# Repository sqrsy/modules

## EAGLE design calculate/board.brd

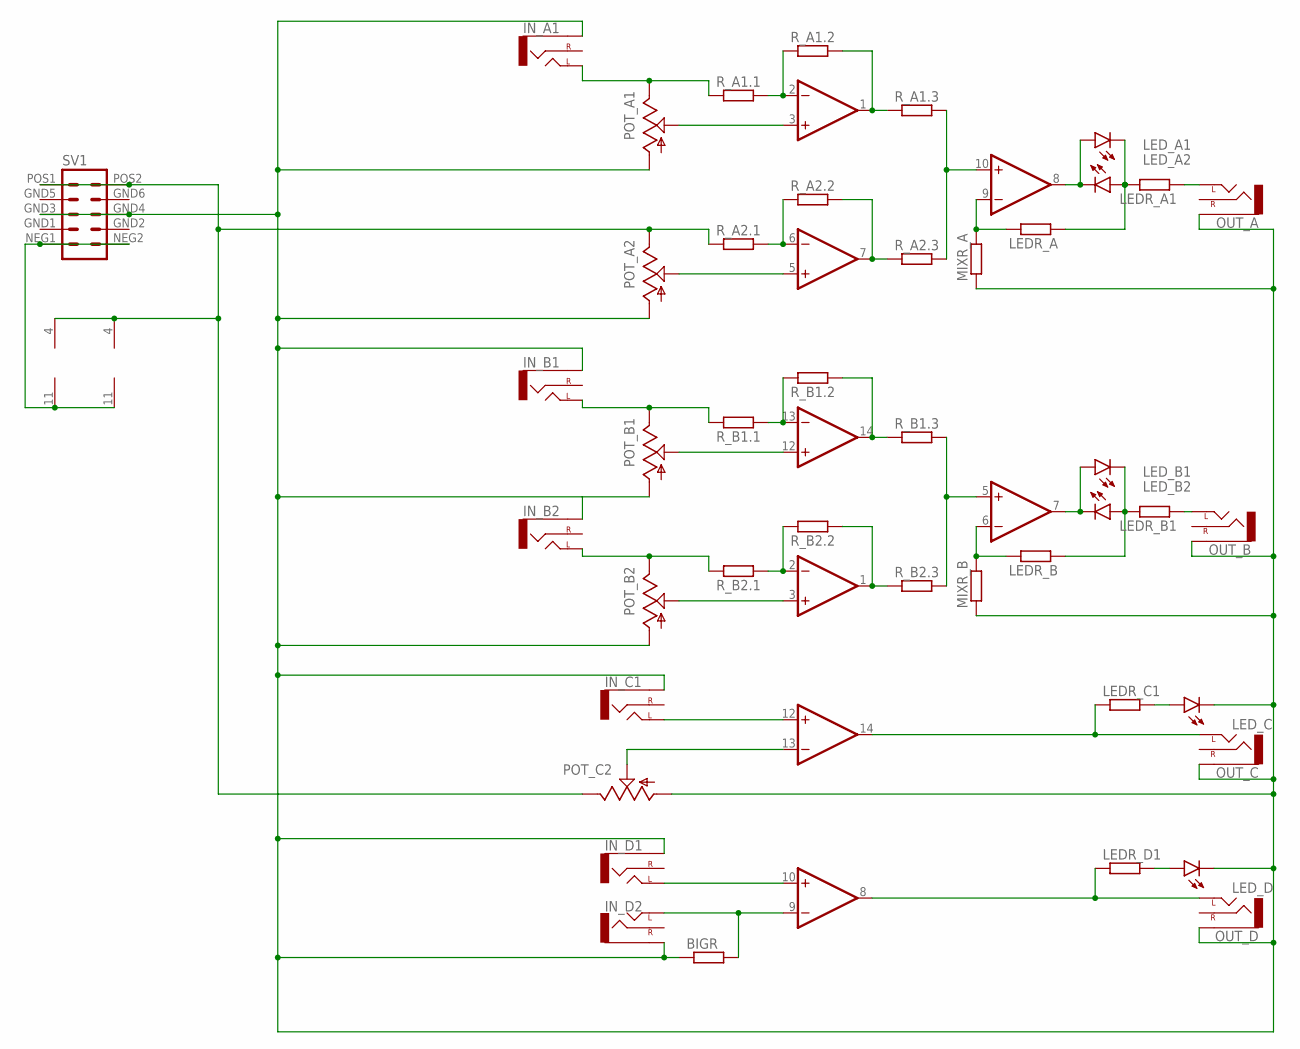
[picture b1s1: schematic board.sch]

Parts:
BIGR: RESISTOR7MM; 7MM_RESISTOR
IC1, IC2: TL074P; DIL14
IN_A1: THONKI-STEREO; WQP-PJ366ST_JACK
IN_B1, IN_B2: THONKI-STEREO; WQP-PJ366ST_JACK
IN_C1: THONKI-STEREO; WQP-PJ366ST_JACK
IN_D1, IN_D2: THONKI-STEREO; WQP-PJ366ST_JACK
LEDR_A, LEDR_A1: RESISTOR7MM; 7MM_RESISTOR
LEDR_B, LEDR_B1: RESISTOR7MM; 7MM_RESISTOR
LEDR_C1: RESISTOR7MM; 7MM_RESISTOR
LEDR_D1: RESISTOR7MM; 7MM_RESISTOR
LED_A1, LED_A2: LED3MM; LED_3MM
LED_B1, LED_B2: LED3MM; LED_3MM
LED_C: LED3MM; LED_3MM
LED_D: LED3MM; LED_3MM
MIXR_A: RESISTOR7MM; 7MM_RESISTOR
MIXR_B: RESISTOR7MM; 7MM_RESISTOR
OUT_A: THONKI-STEREO; WQP-PJ366ST_JACK
OUT_B: THONKI-STEREO; WQP-PJ366ST_JACK
OUT_C: THONKI-STEREO; WQP-PJ366ST_JACK
OUT_D: THONKI-STEREO; WQP-PJ366ST_JACK
POT_A1, POT_A2: 9MM_SNAP-IN_POT_; 9MM_SNAP-IN_POT
POT_B1, POT_B2: 9MM_SNAP-IN_POT_; 9MM_SNAP-IN_POT
POT_C2: 9MM_SNAP-IN_POT_; 9MM_SNAP-IN_POT
R_A1.1, R_A1.2, R_A1.3, R_A2.1, R_A2.2, R_A2.3: RESISTOR7MM; 7MM_RESISTOR
R_B1.1, R_B1.2, R_B1.3, R_B2.1, R_B2.2, R_B2.3: RESISTOR7MM; 7MM_RESISTOR
SV1: EURO_POWER_HEADERLOCK_PADS; EURO_PWR_HEADER_LOCK

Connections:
unnamed: LEDR_A.1, LEDR_A1.2, LED_A1.K (C), LED_A2.A
unnamed: IC2.6 (-IN), LEDR_B.2, MIXR_B.2
unnamed: LEDR_C1.2, LED_C.A
unnamed: IC2.14 (OUT), LEDR_C1.1, OUT_C.P$1_TIP (LEFT)
unnamed: IC1.12 (+IN), POT_B1.2 (S)
unnamed: IC1.4 (V+), IC2.4 (V+), POT_A2.3 (E), POT_C2.3 (E), R_A2.1.1, SV1.POS1 (10), SV1.POS2 (9)
unnamed: IC1.11 (V-), IC2.11 (V-), SV1.NEG1 (2), SV1.NEG2 (1)
unnamed: IC2.13 (-IN), POT_C2.2 (S)
unnamed: IC2.12 (+IN), IN_C1.P$1_TIP (LEFT)
unnamed: IC2.10 (+IN), IN_D1.P$1_TIP (LEFT)
unnamed: BIGR.2, IC2.9 (-IN), IN_D2.P$1_TIP (LEFT)
unnamed: IC2.8 (OUT), LEDR_D1.1, OUT_D.P$1_TIP (LEFT)
unnamed: LEDR_D1.2, LED_D.A
unnamed: LEDR_B.1, LEDR_B1.2, LED_B1.K (C), LED_B2.A
unnamed: IC2.5 (+IN), R_B1.3.2, R_B2.3.2
unnamed: IC2.1 (OUT), R_B2.2.1, R_B2.3.1
unnamed: IC1.14 (OUT), R_B1.2.1, R_B1.3.1
unnamed: IC1.10 (+IN), R_A1.3.2, R_A2.3.2
unnamed: IC1.7 (OUT), R_A2.2.2, R_A2.3.1
unnamed: IC1.1 (OUT), R_A1.2.2, R_A1.3.1
unnamed: IC1.3 (+IN), POT_A1.2 (S)
unnamed: IC1.5 (+IN), POT_A2.2 (S)
unnamed: IN_A1.P$1_TIP (LEFT), POT_A1.3 (E), R_A1.1.1
unnamed: IC1.2 (-IN), R_A1.1.2, R_A1.2.1
unnamed: IC1.6 (-IN), R_A2.1.2, R_A2.2.1
unnamed: IC1.9 (-IN), LEDR_A.2, MIXR_A.2
unnamed: IC1.8 (OUT), LED_A1.A, LED_A2.K (C)
unnamed: LEDR_A1.1, OUT_A.P$1_TIP (LEFT)
unnamed: IC2.3 (+IN), POT_B2.2 (S)
unnamed: IN_B1.P$1_TIP (LEFT), POT_B1.3 (E), R_B1.1.2
unnamed: IN_B2.P$1_TIP (LEFT), POT_B2.3 (E), R_B2.1.2
unnamed: IC2.2 (-IN), R_B2.1.1, R_B2.2.2
unnamed: IC1.13 (-IN), R_B1.1.1, R_B1.2.2
unnamed: IC2.7 (OUT), LED_B1.A, LED_B2.K (C)
unnamed: BIGR.1, IN_A1.P$3_SLEEVE (SLEEVE), IN_B1.P$3_SLEEVE (SLEEVE), IN_B2.P$3_SLEEVE (SLEEVE), IN_C1.P$3_SLEEVE (SLEEVE), IN_D1.P$3_SLEEVE (SLEEVE), IN_D2.P$3_SLEEVE (SLEEVE), LED_C.K (C), LED_D.K (C), MIXR_A.1, MIXR_B.1, OUT_A.P$3_SLEEVE (SLEEVE), OUT_B.P$3_SLEEVE (SLEEVE), OUT_C.P$3_SLEEVE (SLEEVE), OUT_D.P$3_SLEEVE (SLEEVE), POT_A1.1 (A), POT_A2.1 (A), POT_B1.1 (A), POT_B2.1 (A), POT_C2.1 (A), SV1.GND3 (6), SV1.GND4 (5)
unnamed: LEDR_B1.1, OUT_B.P$1_TIP (LEFT)

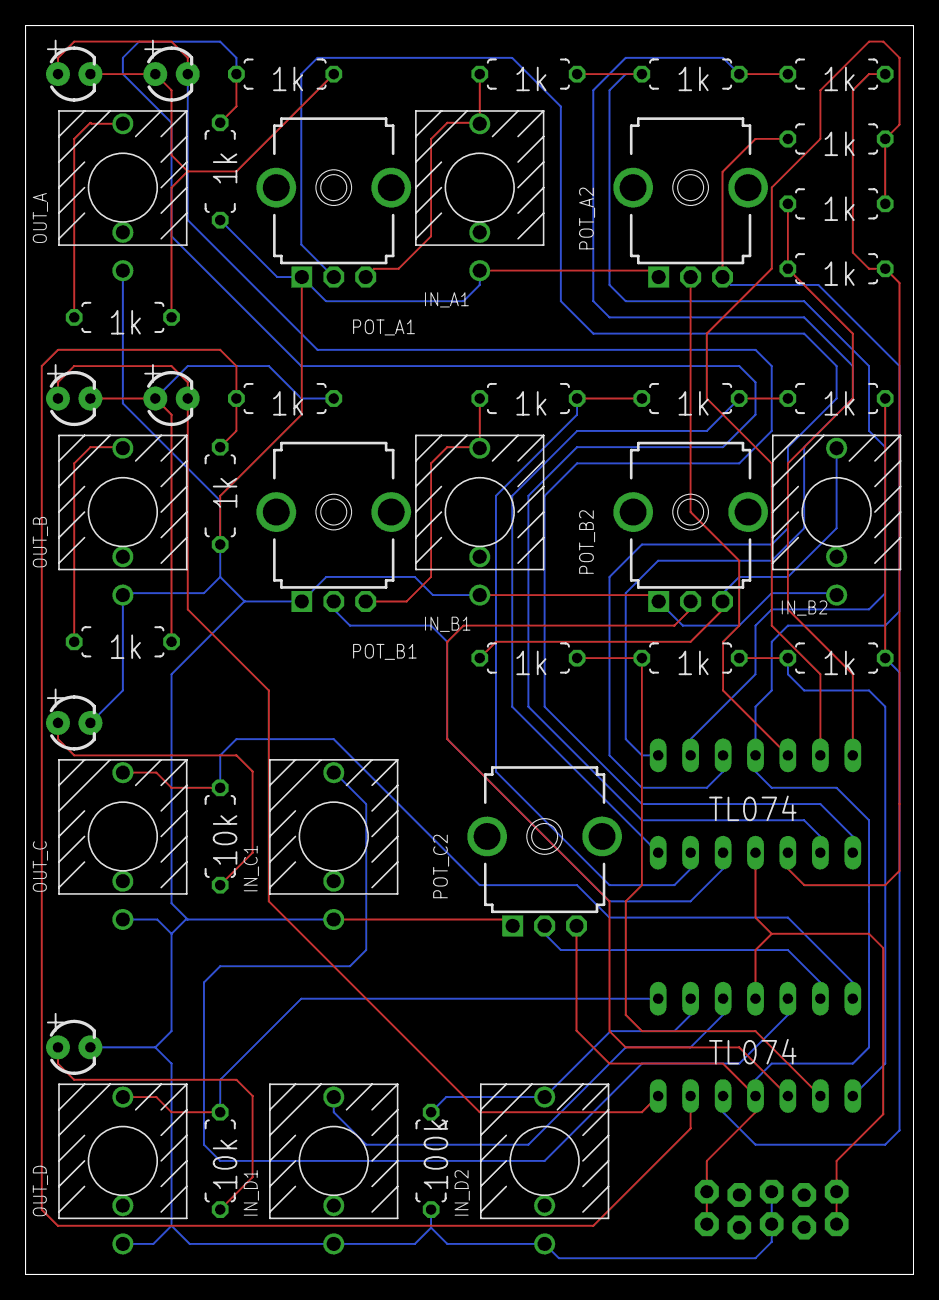
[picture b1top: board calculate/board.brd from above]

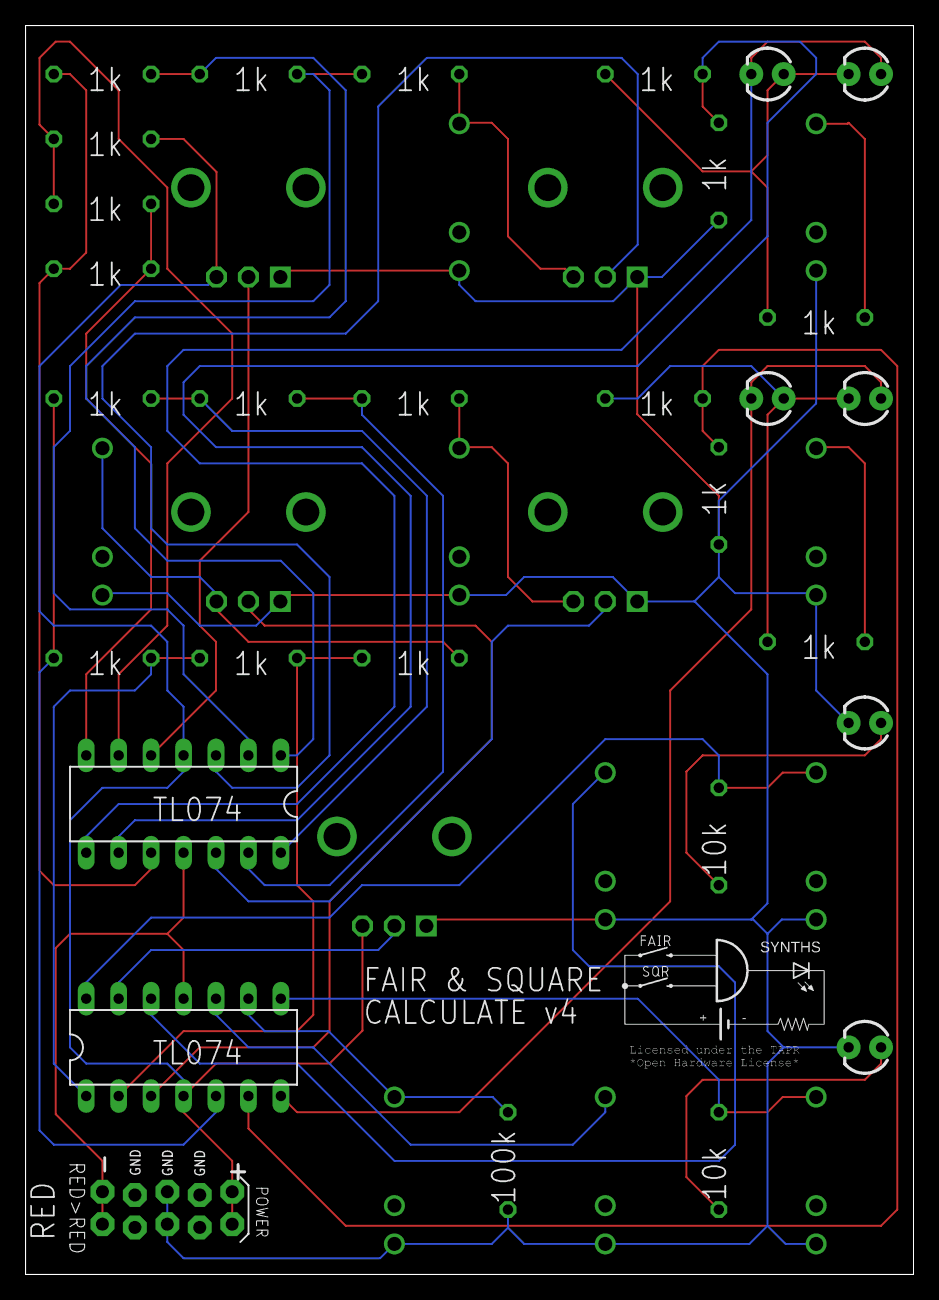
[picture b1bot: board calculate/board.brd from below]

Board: 2 copper layers, 69.5 x 97.8 mm, 45 parts (3 on the bottom side), 36 nets.

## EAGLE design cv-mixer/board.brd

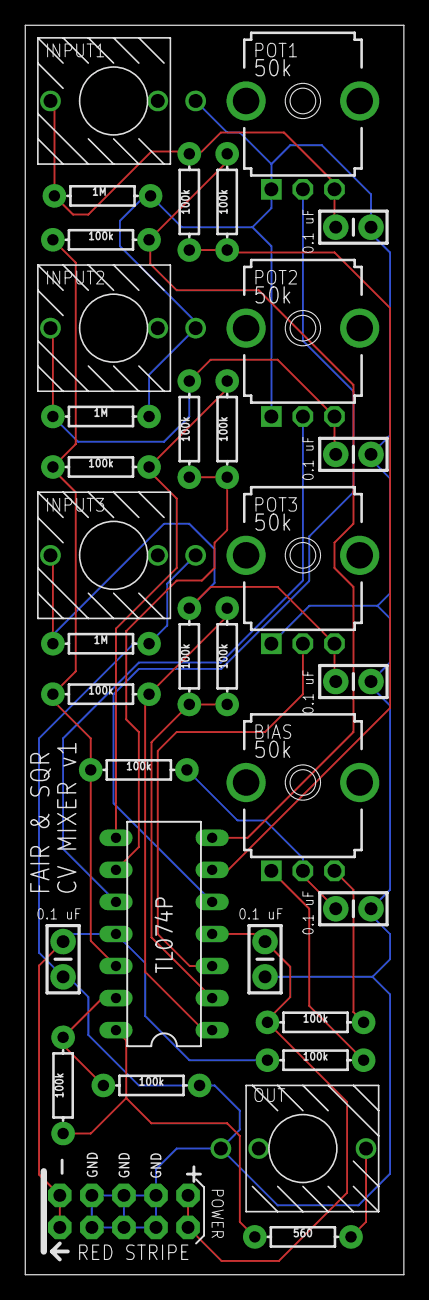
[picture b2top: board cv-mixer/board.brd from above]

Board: 2 copper layers, 30.0 x 99.0 mm, 34 parts (0 on the bottom side), 22 nets.

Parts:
1M1, 1M2, 1M3: 1M; AXIAL-0.3
BIAS: 50k; 9MM_SNAP-IN_POT
BIAS1, BIAS2: 100k; AXIAL-0.3
C1, C2, C3: 0.1uF; CAP-PTH-SMALL-KIT
C_12V: 0.1uF; CAP-PTH-SMALL-KIT
C_-12V: 0.1uF; CAP-PTH-SMALL-KIT
C_BIAS: 0.1uF; CAP-PTH-SMALL-KIT
IC2: TL074P; DIL14
INPUT1, INPUT2, INPUT3: THONKI-STEREO; WQP-PJ366ST_JACK
M1, M2, M3, M4: 100k; AXIAL-0.3
OUT: THONKI-STEREO; WQP-PJ366ST_JACK
POT1, POT2, POT3: 50k; 9MM_SNAP-IN_POT
R1A, R1B, R2A, R2B, R3A, R3B: 100k; AXIAL-0.3
ROUT: 560; AXIAL-0.3
SV1: EURO_POWER_HEADERFAT_PADS; EURO_PWR_HEADER_FAT
UNITY_A: 100k; AXIAL-0.3
UNITY_B: 100k; AXIAL-0.3

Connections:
12V: BIAS1.P$1, C_12V.2, IC2.4, SV1.9, SV1.10
-12V: BIAS2.P$1, C_-12V.2, IC2.11, SV1.1, SV1.2
GND: 1M1.P$2, 1M2.P$2, 1M3.P$2, C1.1, C2.1, C3.1, C_12V.1, C_-12V.1, C_BIAS.2, INPUT1.P$3_SLEEVE, INPUT2.P$3_SLEEVE, INPUT3.P$3_SLEEVE, OUT.P$3_SLEEVE, POT1.1, POT2.1, POT3.1, SV1.3, SV1.4, SV1.5, SV1.6, SV1.7, SV1.8, UNITY_B.P$1
unnamed: OUT.P$1_TIP, ROUT.P$1
unnamed: IC2.14, ROUT.P$2, UNITY_A.P$1
unnamed: BIAS.3, BIAS1.P$2
unnamed: BIAS.1, BIAS2.P$2
unnamed: BIAS.2, C_BIAS.1, M4.P$1
unnamed: IC2.12, M1.P$2, M2.P$2, M3.P$2, M4.P$2
unnamed: IC2.13, UNITY_A.P$2, UNITY_B.P$2
unnamed: IC2.7, M1.P$1, R1B.P$2
unnamed: IC2.6, R1A.P$2, R1B.P$1
unnamed: 1M1.P$1, C1.2, INPUT1.P$1_TIP, POT1.3, R1A.P$1
unnamed: IC2.5, POT1.2
unnamed: IC2.8, M2.P$1, R2B.P$2
unnamed: IC2.9, R2A.P$2, R2B.P$1
unnamed: 1M2.P$1, C2.2, INPUT2.P$1_TIP, POT2.3, R2A.P$1
unnamed: IC2.10, POT2.2
unnamed: IC2.1, M3.P$1, R3B.P$2
unnamed: IC2.2, R3A.P$2, R3B.P$1
unnamed: 1M3.P$1, C3.2, INPUT3.P$1_TIP, POT3.3, R3A.P$1
unnamed: IC2.3, POT3.2

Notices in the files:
parts and their libraries:
SparkFun-LED: Licensing: Creative Commons ShareAlike 4.0 International - https://creativecommons.org/licenses/by-sa/4.0
